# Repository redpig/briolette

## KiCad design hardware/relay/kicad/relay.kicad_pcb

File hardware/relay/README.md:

# Solar Relay — Disconnected Credstick-to-Credstick Payments

## The Problem

The credstick-to-credstick flow requires a phone as NFC relay. But:

- Phone batteries die
- Rural areas may have no electricity for charging
- Some users may not own a smartphone
- Cash works everywhere — Briolette should too

We need a cheap, rugged, batteryless relay device that can facilitate
credstick payments without a phone, without internet, and without
external power.

## The Device: Solar Relay

A small, dedicated NFC reader/writer powered by solar + shake energy.
No screen of its own (or minimal LED indicators). Its only job: shuttle
APDUs between two credsticks, just like the phone PoS relay app.

```
┌──────────────────────────────────────┐
│  ┌──────────────────────────────┐   │
│  │     Solar Panel (top face)   │   │
│  │     ~40x30mm mono-Si cell    │   │
│  └──────────────────────────────┘   │
│                                      │
│  [1] [2] [3] [4]  ← 4 buttons      │
│                                      │
│  ● ● ●  ← 3 LEDs (power/send/recv) │
│                                      │
│  ══════════  NFC reader antenna     │
│  ║  TAP  ║  (marked zone)           │
│  ══════════                          │
│                                      │
│  ┌────────┐                          │
│  │ USB-C  │  ← Charge + firmware    │
│  └────────┘                          │
└──────────────────────────────────────┘
       ~70mm x 45mm x 8mm
```

## Key Difference from Credstick

The credstick is an NFC **tag** (passive, powered by the reader's field).
The relay is an NFC **reader** (active, generates the RF field). This is
the critical distinction — the relay powers the credsticks, not the other
way around.

## Hardware Spec

### Core Components

| Component | Part | Notes |
|-----------|------|-------|
| MCU | nRF52840-QIAA | Same as credstick — shared firmware tooling |
| NFC frontend | PN7150 or PN532 | NFC reader/writer IC (not tag mode) |
| Solar cell | 40x30mm mono-Si | ~80-150mW in direct sun, ~5-15mW shade |
| Supercap | 2x 10F 3V (20F total) | Larger than credstick for reader power |
| Piezo harvester | Same as credstick | Supplemental, for pocket carry |
| Buttons | 4x 3mm tactile switches | PIN entry (see button spec) |
| LEDs | 3x 0402 (R/G/B) | Power status, send, receive |
| USB-C | GCT USB4135-GF-A | Charge + DFU |
| Charge controller | BQ25504 | Ultra-low-power solar MPPT harvester |

### Why PN7150/PN532 Instead of nRF52840's NFC?

The nRF52840's built-in NFC peripheral is **tag-only** (Type 2/4 Tag
emulation). It cannot generate an NFC field or act as a reader. To read
credsticks, we need a dedicated NFC reader IC:

- **PN7150**: NXP's NFC controller with reader/writer + P2P + card
  emulation. I2C interface. Low power (~20mA active). Best option.
- **PN532**: Older but widely available. SPI/I2C/UART. ~100mA active
  (higher power). Good for prototyping.

The nRF52840 drives the PN7150 over I2C and handles the Briolette
protocol logic. The PN7150 handles the RF layer.

### Power Budget

**NFC reader is the expensive part:**

| Operation | Current | Duration | Energy |
|-----------|---------|----------|--------|
| PN7150 field on (reader) | 20-50mA | 3-5s per tap | 60-250mAs |
| nRF52840 active | 5mA | 5s per tap | 25mAs |
| LED indicator | 5mA | 1s | 5mAs |
| Total per tap | | | ~90-280mAs |
| Total per transaction (4 taps) | | | ~360-1120mAs |

At 3V, a single 4-tap transaction costs **~1-3.4J**.

**Supercap budget (20F at 3V):**
- Usable energy: 0.5 x 20 x (9-4) = **50J**
- Transactions per charge: **~15-50**
- USB-C recharge: ~60 seconds

**Solar budget:**
- Direct sun: 80-150mW → 288-540J per hour → **80-160 transactions/hour**
- Overcast: 10-30mW → 36-108J per hour → **10-30 transactions/hour**
- Indoor light: 1-5mW → 3.6-18J per hour → **1-5 transactions/hour**
- Shade outdoors: 5-15mW → 18-54J per hour → **5-15 transactions/hour**

**In direct sun, the relay is effectively unlimited.**

### BQ25504 Solar MPPT

The BQ25504 is a nano-power boost charger with MPPT (Maximum Power Point
Tracking). It efficiently harvests from solar cells as low as 100mV
input and charges the supercap. Key specs:

- Input voltage: 100mV–5.5V (works with any small solar cell)
- Quiescent current: 330nA (virtually zero idle drain)
- MPPT efficiency: 80-90%
- Cold start: 330mV minimum (small light is enough to boot)

This means the relay can cold-start from a dead supercap just by
sitting in sunlight for a few minutes.

## Operating Modes

### 1. Solar Idle (Default)

Solar cell charges supercap via BQ25504. No NFC activity. LEDs off.
Power LED blinks once every 10s to show charge state:
- Green: >50% charge
- Yellow: 20-50%
- Red: <20%

### 2. Transaction Mode (Button Press)

User presses button 1 to start a relay session. The flow mirrors
`receiver.proto` (Initiate → Transact → Transfer):

```
Press [1] → Green LED on → "Ready"

Tap receiver → Blue LED blinks → READ_TICKET (0x11)
              → Blue LED solid → got ticket

Tap sender   → Relay sends INITIATE (0x10) + TRANSACT (0x20)
(tap 1)      → Credstick e-ink shows: "Pay 5 tokens?"
              → Returns unsigned tokens (proposal)
              → Blue LED solid → got proposal

              [User lifts credstick, reads display, enters PIN
               if required — all off the relay]

Tap sender   → Relay sends TRANSFER (0x30) with accept=true
(tap 2)      → Credstick checks PIN was entered (if needed)
              → BLS signs tokens, returns signatures
              → Blue LED solid → got signed tokens

Tap receiver → Relay sends RECEIVE (0x31) with signed tokens
              → Green LED flash 3x → done!
              → (or Red LED flash 3x → failed)
```

**Critical UX: the sender's credstick displays the proposed amount
on its e-ink screen during tap 1, and the user enters PIN between
taps.** The relay cannot forge the amount because the credstick
independently shows the actual APDU payload amount. The user
confirms by choosing to tap again — the physical tap IS consent.
No button press during NFC contact is ever required.

See `button-pin-auth.md` for the full PIN-between-taps flow.

### 3. Fixed-Amount Mode (Merchant Use)

For a merchant who always charges the same amount (e.g., a bus fare):

1. Press and hold [1] during power-on → enters config mode
2. Use buttons [1-4] to set amount (binary or digit-by-digit)
3. Amount is stored in flash
4. Every subsequent button press starts a transaction for that amount

This eliminates the need for a phone entirely for simple, fixed-price
transactions (transit, vending, market stalls).

### 4. Variable-Amount Mode

For variable amounts without a screen, the relay can accept amount
input via button presses:

- Buttons [1-4] map to digits or increments
- Quick-press sequences: [2][3] = 23 tokens
- Long-press [4] = confirm amount
- LED blinks N times to confirm the entered amount

This is clunky but functional. For better UX, pair with a phone running
the PoS app — but the relay works standalone for emergencies.

## PIN Authorization on the Relay

The 4 buttons also serve as PIN entry (see `button-pin-auth.md`).
Before the relay starts a transaction, the operator can optionally
require a PIN:

1. Power on → enter 4-digit PIN via buttons
2. Green LED = authorized, relay is active for N minutes or transactions
3. Wrong PIN → red LED, lockout after 3 failures

This prevents unauthorized use if the relay is stolen.

## BOM (Estimated)

| Component | Qty 10 | Qty 1000 |
|-----------|--------|----------|
| nRF52840 | $3.80 | $3.20 |
| PN7150 | $3.50 | $2.50 |
| Solar cell (40x30mm) | $2.00 | $0.80 |
| BQ25504 | $3.50 | $2.80 |
| Supercaps (2x 10F) | $6.00 | $4.00 |
| Piezo harvester | $5.00 | $2.00 |
| 4x tactile buttons | $0.60 | $0.32 |
| 3x LEDs | $0.30 | $0.15 |
| USB-C connector | $0.60 | $0.35 |
| PCB + passives | $6.00 | $2.00 |
| Enclosure | $3.00 | $0.50 |
| **Total** | **~$34** | **~$19** |

At scale, this is a **sub-$20 device** — comparable to a basic
calculator or kitchen timer. Cheap enough to distribute to rural
merchants or community centers.

## Use Cases

### Rural Market

A village market has no reliable electricity. Each vendor has a solar
relay clipped to their stall. Customers carry credsticks. Payments
happen all day powered by sunlight. At the end of the day, vendors
tap their credstick to a phone (when one is available) to sweep
accumulated tokens to a validated wallet.

### Transit / Bus

A bus driver has a relay mounted on the dashboard. Fixed fare mode.
Passenger taps credstick → fare deducted → rider boards. Solar charges
the relay during the day. USB-C from the bus's 12V system as backup.

### Emergency / Disaster

Grid is down, cell towers are down. People still need to transact.
Solar relays + credsticks provide a fully disconnected, self-powered
payment system. No internet, no electricity, no phone required.

### Peer-to-Peer in the Field

Two hikers want to split a cost. One pulls out a solar relay from their
pack, both tap credsticks. Works on a mountaintop with zero infrastructure.

## Credstick Storage Considerations

For long periods of disconnected operation, credsticks accumulate
unvalidated tokens. The credstick flash should accommodate:

| Scenario | Tokens | Storage (~200 bytes/token) |
|----------|--------|---------------------------|
| Light daily use (5 txns/day, 7 days) | 35 | ~7 KB |
| Heavy daily use (20 txns/day, 7 days) | 140 | ~28 KB |
| Extended disconnected (30 days) | 600 | ~120 KB |
| Extreme (3 months disconnected) | 1800 | ~360 KB |

The nRF52840 has 1 MB flash. After firmware (~256 KB) and bloom
filter (~64 KB), there's **~680 KB** available for token storage —
enough for ~3400 tokens, covering months of disconnected operation.

For extra safety, an external QSPI flash (e.g., 4 MB MX25R4035F, $0.50)
could extend storage to tens of thousands of tokens.

## Relationship to Phone PoS App

The solar relay and the phone PoS app are functionally identical — both
are dumb NFC relays that shuttle APDUs. The difference:

| | Phone PoS App | Solar Relay |
|---|---------------|-------------|
| Screen | Full touchscreen | 3 LEDs |
| Input | Touch keyboard | 4 buttons |
| Power | Phone battery | Solar + supercap |
| Cost | $0 (app on existing phone) | ~$19 at scale |
| Internet | Optional (for logging) | Never needed |
| UX | Rich, guided | Minimal, LED-guided |

They're complementary. The phone app is better UX. The solar relay is
the fallback when phones aren't available.

## Future: Deposit Box Mode (v2)

Beyond real-time relay, the solar relay can evolve into a **deposit box**
("cryptographic village bank") for deferred payments. See
`../stick/docs/deferred-payment.md` for the full design.

In this mode, senders prepare and sign payments on their credstick alone
(using a saved recipient code), then drop off pre-signed tokens at the
relay later. Recipients collect deposits by tapping the relay and proving
ticket ownership.

### Relay Storage for Deposits

The v1 relay hardware should account for this by including external flash:

| Storage | Capacity | Deposits (~300 bytes each) | Cost |
|---------|----------|---------------------------|------|
| nRF52840 internal (spare) | ~200 KB | ~600 | $0 |
| External QSPI (MX25R4035F) | 4 MB | ~13,000 | ~$0.50 |

For a village relay serving a few dozen daily transactions, internal flash
suffices. The QSPI footprint should be on the v1 PCB even if not populated
initially — allows the upgrade path without a board respin.

### Merchant Registry

The relay can store a local registry mapping short codes (e.g., "001") to
merchant `SignedTicket` data. This enables the "type in merchant code on
credstick, resolve at relay" flow. Storage: ~300 bytes per merchant ×
100 merchants = ~30 KB. Trivially fits in flash.

### APDU Reservations

The v1 relay firmware should reserve INS bytes 0x40-0x4F for deposit box
commands (DROP_OFF, CHECK_DEPOSITS, COLLECT). No implementation needed
for v1 — just don't assign those bytes to other functions.

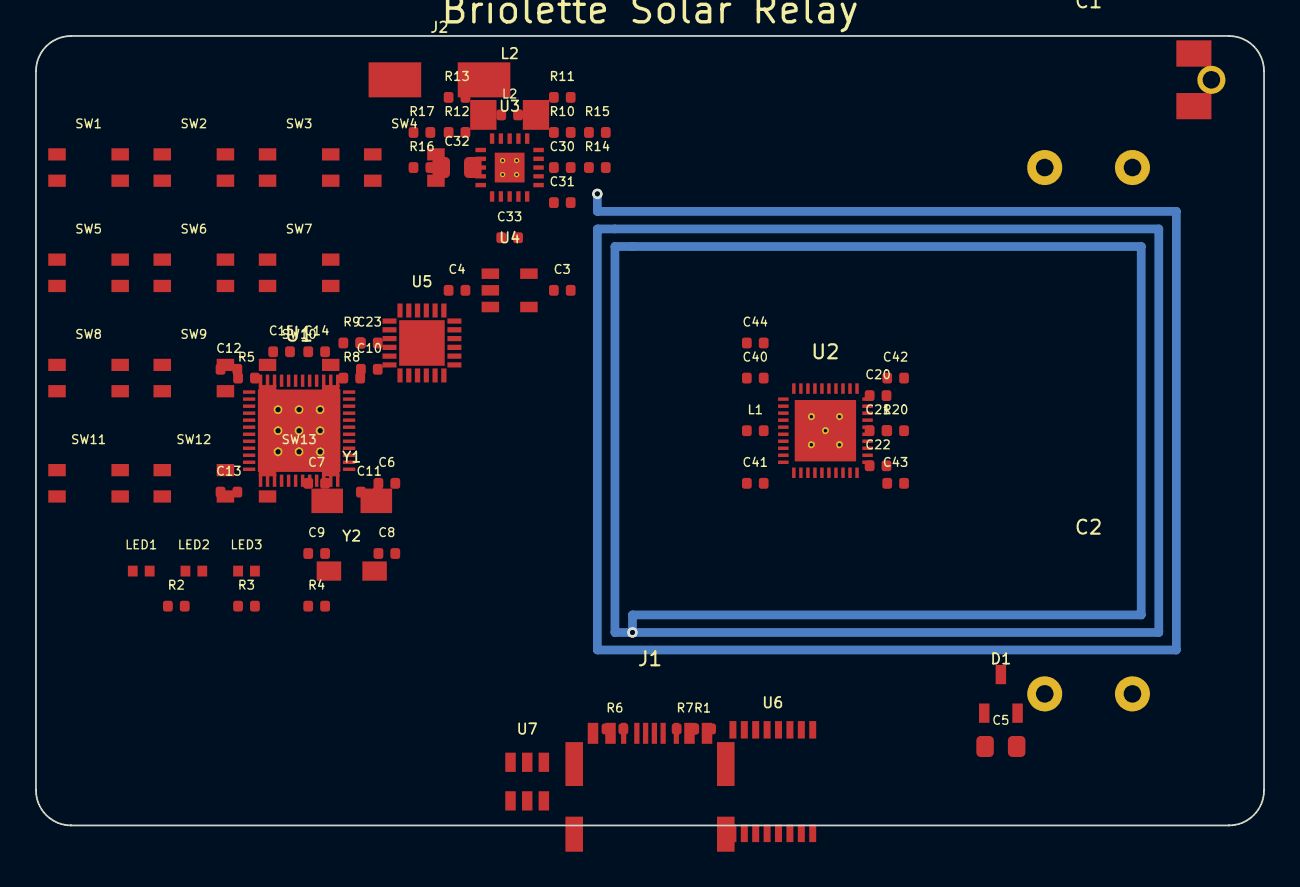
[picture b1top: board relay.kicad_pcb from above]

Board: 4 copper layers, 70.0 x 45.0 mm, 78 parts (0 on the bottom side), 33 nets.

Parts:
C1, C2: 10F 3V; Supercap_Cylindrical_14mm
C3, C4, C33: 10uF; C_0402_1005Metric
C5: 100uF; C_0805_2012Metric
C6, C7: 12pF; C_0402_1005Metric
C8, C9: 6.8pF; C_0402_1005Metric
C10, C11, C12, C13, C14, C15, C20, C21, C22, C23, C30, C43, C44: 100nF; C_0402_1005Metric
C31: 4.7uF; C_0402_1005Metric
C32: 22uF; C_0805_2012Metric
C40, C41: 150pF; C_0402_1005Metric
C42: 27pF; C_0402_1005Metric
D1: BAT54S; SOT-23
J1: USB4135-GF-A; USB_C_GCT_USB4135
J2: Solar_Cell; SolderWirePad_1x02_P5.08mm_D1.5mm
J3: PPA-1014; Piezo_Cantilever_25x5mm
L1: 390nH; L_0402_1005Metric
L2: 2.2uH; L_0402_1005Metric
L2#2: 2.2uH; L_Coilcraft_LPS4018
LED1: RED; LED_0402_1005Metric
LED2: GREEN; LED_0402_1005Metric
LED3: BLUE; LED_0402_1005Metric
R1, R5: 10k; R_0402_1005Metric
R2, R3, R4: 1k; R_0402_1005Metric
R6, R7: 5.1k; R_0402_1005Metric
R8, R9: 4.7k; R_0402_1005Metric
R10, R12, R14, R16: 5.76M; R_0402_1005Metric
R11: 8.06M; R_0402_1005Metric
R13, R17: 8.87M; R_0402_1005Metric
R15: 13.3M; R_0402_1005Metric
R20: 10R; R_0402_1005Metric
SW1: KEY_1; SW_SPST_3x3mm
SW2: KEY_2; SW_SPST_3x3mm
SW3: KEY_3; SW_SPST_3x3mm
SW4: KEY_CLR; SW_SPST_3x3mm
SW5: KEY_4; SW_SPST_3x3mm
SW6: KEY_5; SW_SPST_3x3mm
SW7: KEY_6; SW_SPST_3x3mm
SW8: KEY_7; SW_SPST_3x3mm
SW9: KEY_8; SW_SPST_3x3mm
SW10: KEY_9; SW_SPST_3x3mm
SW11: KEY_DOT; SW_SPST_3x3mm
SW12: KEY_0; SW_SPST_3x3mm
SW13: KEY_OK; SW_SPST_3x3mm
U1: nRF52840; QFN-48-6x6mm
U2: PN7150; HVQFN-40-5x5mm
U3: BQ25504; QFN-20-3.5x3.5mm
U4: AP2112K-3.3; SOT-23-5
U5: TCA8418; WQFN-24-4x4mm
U6: IP4292CZ12; TSSOP-16_4.4x5mm_P0.65mm
U7: TPS2553; SOT-23-6
Y1: 32MHz; Crystal_SMD_3225-2Pin_3.2x2.5mm
Y2: 32.768kHz; Crystal_SMD_3215-2Pin_3.2x1.5mm

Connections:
GND: C1.2, C2.2, C3.2, C4.2, C5.2, C6.2, C7.2, C8.2, C9.2, C10.2, C11.2, C12.2, C13.2, C14.2, C15.2, C20.2, C21.2, C22.2, C23.2, C30.2, C31.2, C32.2, C33.2, C40.2, C41.2, C42.2, C43.2, C44.2, J1.A1, J1.B1, J1.S1, J2.2, J3.2, J3.MP, LED1.2, LED2.2, LED3.2, R1.2, R6.2, R7.2, R11.2, R13.2, R15.2, R17.2, U1.33, U1.39, U1.49, U2.1, U2.2, U2.8, U2.11, U2.24, U2.25, U2.30, U2.37, U2.41, U3.2, U3.14, U3.17, U3.21, U4.2, U5.24, U5.25, U6.8, U6.9, U7.2
I2C_SCL: R9.2, U1.31, U2.10, U5.15
I2C_SDA: R8.2, U1.30, U2.9, U5.14
KEY_COL0: SW1.1, SW1.3, SW5.1, SW5.3, SW8.1, SW8.3, SW11.1, SW11.3, U5.7
KEY_COL1: SW2.1, SW2.3, SW6.1, SW6.3, SW9.1, SW9.3, SW12.1, SW12.3, U5.8
KEY_COL2: SW3.1, SW3.3, SW7.1, SW7.3, SW10.1, SW10.3, SW13.1, SW13.3, U5.9
KEY_COL3: SW4.1, SW4.3, U5.10
KEY_INT: U1.15, U5.16
KEY_ROW0: SW1.2, SW1.4, SW2.2, SW2.4, SW3.2, SW3.4, SW4.2, SW4.4, U5.1
KEY_ROW1: SW5.2, SW5.4, SW6.2, SW6.4, SW7.2, SW7.4, U5.2
KEY_ROW2: SW8.2, SW8.4, SW9.2, SW9.4, SW10.2, SW10.4, U5.3
KEY_ROW3: SW11.2, SW11.4, SW12.2, SW12.4, SW13.2, SW13.4, U5.4
KEY_RST: U1.16, U5.19
LBST: L2.1, L2#2.1, U3.18, U3.19
LED_B: LED3.1, R4.2, U1.14
LED_G: LED2.1, R3.2, U1.12
LED_R: LED1.1, R2.2, U1.11
NFC_IRQ: U1.25, U2.7
NFC_RX: C42.1, R20.1, R20.2, U2.23
NFC_TX1: C40.1, L1.1, L1.2, U2.28
NFC_TX2: C41.1, U2.29
NFC_VEN: U1.26, U2.35
USB_DM: J1.A7, J1.B7, U6.1, U6.16
USB_DP: J1.A6, J1.B6, U6.2, U6.15
VBAT_OK: U1.9, U3.9
VBUS: C5.1, D1.3, J1.A4, J1.B4, U6.5, U6.12, U7.1, U7.3
VCC: C3.1, C10.1, C11.1, C12.1, C13.1, C14.1, C15.1, C20.1, C21.1, C22.1, C23.1, C43.1, C44.1, R2.1, R3.1, R4.1, R5.1, R8.1, R9.1, U1.3, U1.13, U1.42, U1.43, U2.3, U2.4, U2.5, U2.26, U2.27, U2.38, U4.5, U5.13
VSCAP: C1.1, C2.1, C4.1, C31.1, C32.1, C33.1, D1.1, D1.2, R10.1, R12.1, R14.1, U3.7, U3.8, U3.15, U3.16, U4.1, U4.3, U7.6
VSOLAR: C30.1, J2.1, J3.1, L2.2, L2#2.2, R16.1, U3.1, U3.20
XC1: C6.1, Y1.1
XC2: C7.1, Y1.2
XL1: C8.1, U1.5, Y2.1
XL2: C9.1, U1.6, Y2.2

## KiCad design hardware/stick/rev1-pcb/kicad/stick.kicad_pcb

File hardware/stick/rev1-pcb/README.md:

# Rev 1 — Custom PCB

First integrated board. All components on a single PCB targeting a
keychain or USB-stick form factor.

## Target Form Factor

**Keychain fob / thick USB stick:**
- ~60mm x 30mm x 6mm (roughly the size of a car key fob)
- USB-C connector on one end
- E-ink display window on one face
- NFC antenna as PCB trace coil (no external antenna)
- Keyring hole on opposite end from USB-C

```
  ┌─────────────────────────────────────────┐
  │  ○  ┌─────────────────────┐             │
  │ key │                     │  ┌────────┐ │
  │ring │    E-Ink Display    │  │ USB-C  │ │
  │     │     1.02" / 1.54"   │  └────────┘ │
  │     └─────────────────────┘             │
  │     [◄]                 [►]             │
  │    ╔══════════════════════════╗          │
  │    ║   NFC Trace Antenna     ║          │
  │    ╚══════════════════════════╝          │
  └─────────────────────────────────────────┘
         ~60mm x 30mm (top view)
```

The two buttons [◄] [►] sit below the display, aligned with the
"No" and "Yes" labels shown during transaction confirmation. They
also serve as PIN entry (left/right + timing), balance navigation,
and general UI control. See `docs/button-pin-auth.md` for details.

## Layer Stack (4-layer PCB)

| Layer | Purpose |
|-------|---------|
| Top | Components, USB-C, display connector, buttons |
| Inner 1 | Ground plane |
| Inner 2 | Power plane + I2C/SPI routing |
| Bottom | NFC antenna trace coil |

## Block Diagram

```
                    USB-C
                      │
              ┌───────┴───────┐
              │  ESD Protect   │
              │  (IP4292CZ12)  │
              └───────┬───────┘
                      │ VBUS
              ┌───────┴───────┐     ┌──────────────────┐
              │  Charge path   │     │ Supercaps        │
              │  (current-     │─────│ 2× 5F 3V (par.) │
              │  limited)      │     │ = 10F total      │
              └───────────────┘     └────────┬─────────┘
                                             │ VSCAP (2.0-3.0V)
              ┌──────────────────────────────┴─┐
              │  LDO or buck-boost               │
              │  (3.0V → stable 3.3V or direct)  │
              └───────────┬─────────────────────┘
                          │ VCC
              ┌───────────┴───────────┐
              │       nRF52840        │     ┌──────────────┐
              │       (QFN-48)        │─7816│  SIM Card    │
              │                       │     │  (nano-SIM)  │
              │  CryptoCell 310       │     │  push-push   │
              │                       │     └──────────────┘
              │  NFC1/NFC2 ───────────┼──── PCB Trace Antenna
              │                       │
              │  SPI ─────────────────┼──── E-Ink Display (FPC)
              │                       │
              │  GPIO ────────────────┼──── Button(s) + Piezo
              └───────────────────────┘

              ┌───────────────────────┐
              │  Piezo Harvester      │
              │  (cantilever + rect.) │──── VSCAP (trickle)
              └───────────────────────┘
```

## Design Files

KiCad project files will be added here as the design progresses.

```
rev1-pcb/
├── README.md          # This file
├── BOM.md             # Production bill of materials
├── kicad/             # KiCad project (future)
│   ├── stick.kicad_pro
│   ├── stick.kicad_sch
│   └── stick.kicad_pcb
├── gerbers/           # Manufacturing files (future)
└── 3d/                # Enclosure models (future)
```

## Design Decisions

- **nRF52840 QFN-48** (not WLCSP): QFN is hand-solderable with hot air
  for prototyping. WLCSP requires reflow and X-ray inspection.
- **Nano-SIM push-push connector** (Molex 78800-0001): Low-profile
  (1.25mm height), flush-insert push-push mechanism. ISO 7816 interface
  (SIM_IO, SIM_CLK, SIM_RST). User-replaceable SIM card provides the
  same tamper-resistant SE functions as the old ATECC608B (P-256 ECDSA,
  key storage, monotonic counters) but is swappable and field-upgradeable.
  Production-robust: standard connector used in billions of phones.
- **NFC as PCB trace**: Eliminates a discrete antenna component. The
  bottom copper layer has a rectangular spiral trace tuned to 13.56 MHz
  with a matching network (two capacitors).
- **Supercapacitors (2× 5F 3V in parallel = 10F)**: Primary energy
  storage. Infinite cycle life (>1M cycles), no degradation, no fire
  risk, wide temperature range. 25J stored, ~96 transactions per full
  charge. Self-discharge (~5-10%/day) offset by piezo harvesting.
  USB-C recharge takes seconds, not hours.
- **Piezo energy harvester**: Cantilever-mounted piezoelectric element
  converts keychain motion into electrical energy. Passive carry offsets
  supercap self-discharge; deliberate shaking adds ~10-50mJ in 10s.
  Rectified via a Schottky bridge + small buffer cap into VSCAP rail.
- **No battery**: Deliberate choice for infinite device lifetime. No
  capacity fade, no swelling, no replacement needed. The supercap +
  piezo + USB-C combination covers all use cases.
- **1.02" e-ink preferred**: Smaller display fits the keychain target.
  128x80 pixels is enough for balance + 2-line status. The 1.54" is an
  option if we relax to credit-card size.

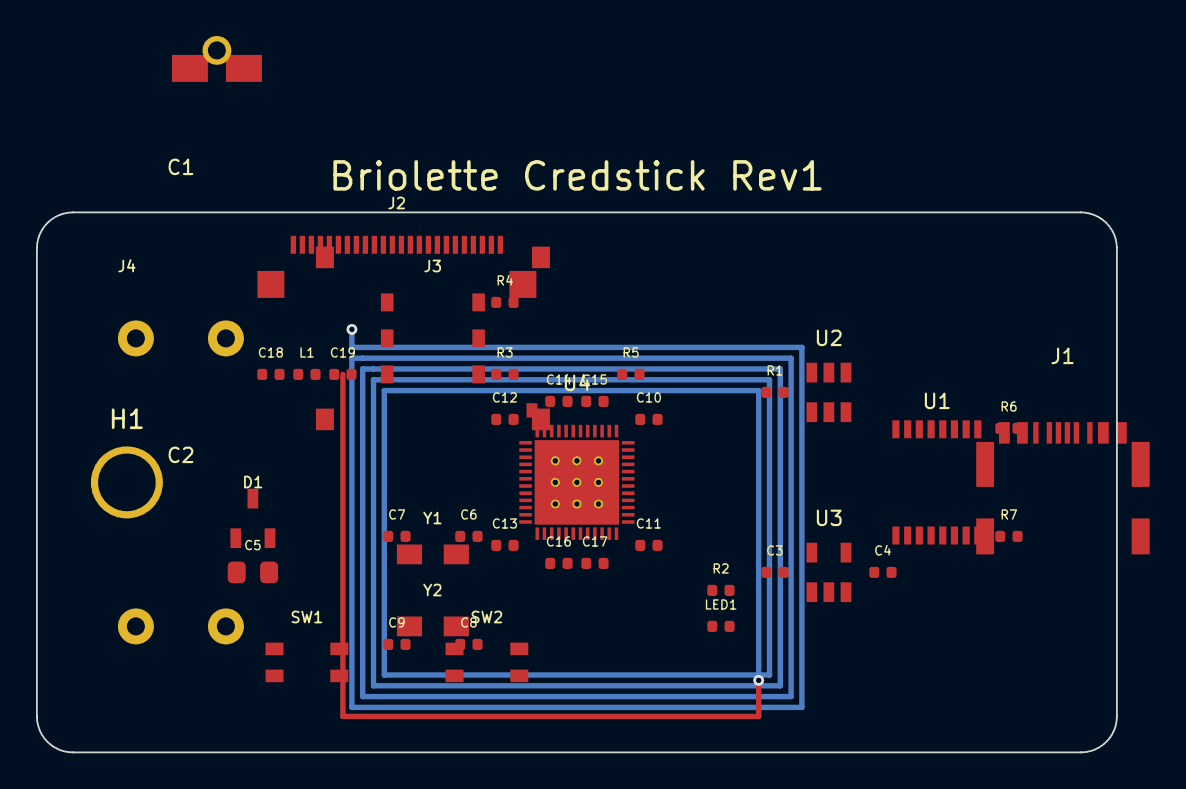
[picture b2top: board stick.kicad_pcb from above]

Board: 4 copper layers, 60.0 x 30.0 mm, 42 parts (0 on the bottom side), 32 nets.

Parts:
C1, C2: 5F 3V; Supercap_Cylindrical_14mm
C3, C4: 10uF; C_0402_1005Metric
C5: 100uF; C_0805_2012Metric
C6, C7: 12pF; C_0402_1005Metric
C8, C9: 6.8pF; C_0402_1005Metric
C10, C11, C12, C13, C14, C15, C16, C17: 100nF; C_0402_1005Metric
C18, C19: 180pF; C_0402_1005Metric
D1: BAT54S; SOT-23
H1: Keyring; MountingHole_3.2mm_M3
J1: USB4135-GF-A; USB_C_GCT_USB4135
J2: GDEY0154D67; FPC_24pin_0.5mm
J3: Nano-SIM Push-Push; NanoSIM_Molex_78800
J4: PPA-1014; Piezo_Cantilever_25x5mm
L1: 390nH; L_0402_1005Metric
LED1: Green; LED_0402_1005Metric
R1, R3, R4, R5: 10k; R_0402_1005Metric
R2: 1k; R_0402_1005Metric
R6, R7: 5.1k; R_0402_1005Metric
SW1: BTN_L; SW_SPST_3x3mm
SW2: BTN_R; SW_SPST_3x3mm
U1: IP4292CZ12; TSSOP-16_4.4x5mm_P0.65mm
U2: TPS2553; SOT-23-6
U3: AP2112K-3.3; SOT-23-5
U4: nRF52840; QFN-48-6x6mm
Y1: 32MHz; Crystal_SMD_3225-2Pin_3.2x2.5mm
Y2: 32.768kHz; Crystal_SMD_3215-2Pin_3.2x1.5mm

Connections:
BTN_L: SW1.1, SW1.3, U4.34
BTN_R: SW2.1, SW2.3, U4.35
CC1: J1.A5, R6.1
CC2: J1.B5, R7.1
DEC1: C14.1, U4.27
DEC4: C15.1, U4.10
EPD_BUSY: J2.18, U4.43
EPD_DC: J2.16, U4.41
EPD_RST: J2.17, U4.42
GND: C1.2, C2.2, C3.2, C4.2, C5.2, C6.2, C7.2, C8.2, C9.2, C10.2, C11.2, C12.2, C13.2, C14.2, C15.2, C16.2, C17.2, C18.2, C19.2, D1.3, J1.A1, J1.B1, J1.S1, J2.1, J2.2, J2.12, J2.MP, J3.C5, J3.SH, LED1.2, R1.2, R2.2, R6.2, R7.2, SW1.2, SW1.4, SW2.2, SW2.4, U1.8, U1.9, U2.2, U3.2, U4.49
ILIM: R1.1, U2.4
LED: LED1.1, R2.1, U2.5, U4.46
NFC1: C18.1, L1.1, U4.32
NFC_ANT1: C19.1, L1.2
PIEZO_P: D1.1, J4.1
SIM_CLK: J3.C3, U4.15
SIM_DET: J3.CD, R4.2, U4.48
SIM_IO: J3.C7, R3.2, U4.14
SIM_RST: J3.C2, U4.47
SPI_CS: J2.15, U4.40
SPI_MOSI: J2.14, U4.39
SPI_SCK: J2.13, U4.38
USB_DM: J1.A7, J1.B7, U1.1, U1.16, U4.6
USB_DP: J1.A6, J1.B6, U1.2, U1.15, U4.7
VBUS: J1.A4, J1.B4, U1.5, U1.12, U2.1, U4.8
VCC: C4.1, C10.1, C11.1, C12.1, C13.1, C16.1, C17.1, J2.11, J3.C1, J3.C6, R3.1, R4.1, R5.1, U3.5, U4.5, U4.12, U4.20, U4.28, U4.37
VSCAP: C1.1, C2.1, C3.1, C5.1, D1.2, U2.6, U3.1, U3.3, U4.16
XC1: C6.1, U4.3, Y1.1
XC2: C7.1, U4.2, Y1.2
XL1: C8.1, U4.25, Y2.1
XL2: C9.1, U4.26, Y2.2
~RESET: R5.2, U4.36

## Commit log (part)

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2026-03-09 fix: correct truncated crate imports in wallet tests
    The wallet test module had truncated import names (ette_clerk, ette_registrar)
    instead of the full crate names (briolette_clerk, briolette_registrar),
    preventing test compilation.
    https://claude.ai/code/session_01DAqwMnBQGaP2NES63jLv2t
2026-03-09 Replace xaptum ECDAA C library with pure Rust implementation
    Replace the C FFI wrapper around libecdaa with a native Rust ECDAA
    implementation using substrate-bn (BN254 pairing-friendly curve).
    The public API in v0.rs is preserved: generate_wallet_keypair,
    generate_issuer_keypair, issue_credential, sign, verify,
    randomize_credential, credential_from_signature, deflate/inflate
    signature, and credential_in_group all maintain the same signatures
2026-03-10 Add split-key signing protocol (Brickell & Li style)
    Implements additive key splitting for ECDAA signatures where
    sk = card_sk + host_sk. The smart card only performs G1 scalar
    multiplications and Fr arithmetic — no pairings needed on-card.
    This enables Javacard/SIM-based wallets following the PAYGO model.
    Includes SmartCard trait, MockCard implementation, split key
    generation, split signing protocol, and 19 tests covering
2026-03-10 Validate split amounts in token_is_extension to prevent value inflation
    token_is_extension() previously accepted extensions containing split tags
    without checking whether the split amount exceeded the token's original
    descriptor value. A malicious wallet could extend a token history with
    an inflated split amount (e.g., claiming 15 on a token worth 10) and
    have it accepted as a legitimate extension.
    Now checks all new history entries for SplitValue tags and rejects the
2026-03-10 Add analysis of spending off expired tickets during partitions
    During a network partition, a wallet's short-lived tickets expire while
    tokens remain bound to them. The design already allows transfers to
    expired tickets (clerk.proto:32), and Token::transfer() doesn't check
    expiration. But SignedTicket::verify() rejects expired tickets in
    historical entries, freezing the tokens.
    Proposes relaxing verification: only enforce ticket expiration on the
2026-03-11 Add Bitcoin L2 bridge implementation alongside Ethereum
    Adds a parallel Bitcoin L1 integration for Briolette, enabling it to
    operate as either an Ethereum or Bitcoin L2. Both implementations coexist
    in the same codebase for reference comparison.
    New files:
    - l1.rs: Chain-agnostic L1Client trait extracted from ethereum.rs
    - bitcoin.rs: Bitcoin L1 client using Taproot deposits, OP_RETURN epoch
2026-03-11 Add Terminated stutter step to GossipConvergence
    Prevents deadlock when all honest wallets converge at MaxEpoch
    and no further actions are enabled. Same pattern as the other specs.
    Verified: 81 distinct states, all safety invariants + EventualConvergence
    liveness hold.
    https://claude.ai/code/session_01GwHJwU12qdRAMvY17Pi1iQ
2026-03-11 Add A2A and x402 protocol support for agent commerce
    Implements two complementary HTTP protocols on top of briolette's
    existing gRPC infrastructure:
    - A2A (Agent-to-Agent): Agent Card discovery at /.well-known/agent.json
    and JSON-RPC 2.0 task lifecycle mapping Receiver's initiate/transact/
    transfer flow to A2A task states.
    - x402 (HTTP 402 Payment Required): axum middleware that paywalls HTTP
2026-03-11 Add QR scanner, transfer display, history, and iOS Compose integration
    Completes the core mobile wallet UX with all QR-based payment flows:
    CameraX + ML Kit QR scanner (Android):
    - Full-screen camera preview with barcode analysis
    - Runtime camera permission request
    - Viewfinder overlay and scan-once guard
    - Automatic QR format detection (raw base64 or JSON envelope)
2026-03-11 Add hardware attestation verification for Android and iOS registrar
    Implement Android Key Attestation (X.509 cert chain with ASN.1
    KeyDescription) and iOS App Attest (CBOR attestation object with x5c)
    verification in the registrar. The registrar now verifies real hardware
    attestation before issuing ECDAA credentials, binding TTC nonces to
    hardware-derived identifiers instead of self-reported hw_id.
    - Add attestation.rs with verify_android_attestation() and
2026-03-11 Add proto definitions for security-level-tiered policy
    Add SecurityLevelPolicy and SecurityLevelGroupKeys messages to
    ExtendedEpochData, and granted_security_level field to RegisterReply.
    This is the proto groundwork for differentiating ticket lifetime and
    other policies based on hardware attestation security level (LOW for
    software-only wallets, HIGH for smartcard-backed wallets).
    https://claude.ai/code/session_01TM1rFxbipYtvAkh4Vt7My7
2026-03-11 Allow user to freely choose MEDIUM or HIGH security mode
    Remove the NFC hardware gate on the High chip so users can always
    select either mode. When HIGH is chosen without NFC available, a
    warning is shown instead of disabling the option.
    https://claude.ai/code/session_01TM1rFxbipYtvAkh4Vt7My7
2026-03-12 Add compile-time conditional for EC math backend
    Split ECMath into two implementations selected at build time:
    - applet-sim/ECMath.java: BigInteger (jCardSim simulator, default)
    - applet-hw/ECMath.java: JCMathLib (production JavaCard hardware)
    The build system automatically selects the backend based on whether
    JCMATHLIB_HOME is set or libs/JCMathLib.jar exists. Can also be
    forced with -PUSE_JCMATHLIB=true.
2026-03-12 Correct H-2 finding: JavaCard EC math stubs replaced with real implementations
    The applet now has two ECMath backends:
    - applet-sim/ECMath.java: BigInteger-based for jCardSim testing
    - applet-hw/ECMath.java: JCMathLib-based for real JavaCard hardware
    BrioletteApplet delegates to ECMath.* static methods; build flag selects
    backend. Downgrade from High to Medium — remaining work is hardware testing.
    https://claude.ai/code/session_01TM1rFxbipYtvAkh4Vt7My7
2026-03-12 Switch v1 (BLS12-381) to compressed point serialization
    Use Zcash/IETF compressed encoding for G1 (48 bytes) and G2 (96 bytes)
    instead of uncompressed (97/193 bytes). This makes v1 ECDAA signatures
    288 bytes — 19% smaller than v0's 356 bytes — while providing 128-bit
    security vs v0's ~100-bit.
    Key size changes:
    - G1: 97 → 48 bytes, G2: 193 → 96 bytes
2026-03-12 Add wallet recovery system: design doc, proto, TLA+ spec, and implementation
    Implements the recovery server and proof-of-binding protocol for recovering
    tokens from lost wallets. Wallets pre-register a recovery binding (ECDSA P-256
    backup key or peer wallet TTC credential) with the recovery server. After loss,
    the delegate proves authorization and receives replacement tokens from the mint.
    The old wallet's credential group is revoked to prevent double-spending.
    New files:
2026-03-13 Document NAC attestation architecture and manufacturer DAA vision
    Add docs/design/nac_attestation.md covering:
    - Why BLS12-381 keys can't live in platform keystores (P-256/RSA only)
    - How P-256 attestation gates NAC credential issuance (current model)
    - Target: manufacturer DAA credentials for smartcard attestation
    - Alternative: platform keystore pairing-friendly curve support
    - Security tier progression: LOW → MEDIUM → HIGH → HIGH+ → Ideal
2026-03-13 Supercap-primary power design, piezo harvesting, credstick-to-credstick protocol
    Power architecture reworked:
    - Supercaps (2x5F 3V) as sole energy storage — infinite cycle life
    - Piezo energy harvester offsets self-discharge from keychain motion
    - No battery: device lifetime limited only by component failure
    - 10F supercap supports 100+ transactions per USB-C charge (~30s)
    New doc: credstick-to-credstick payments via phone relay
2026-03-13 Add KiCad project for credstick Rev1 PCB (60x30mm, 4-layer)
    Hierarchical schematic with three sheets:
    - Power: USB-C → ESD (IP4292CZ12) → charge limiter (TPS2553) →
    supercaps (2×5F 3V) → LDO (AP2112K-3.3), plus piezo harvester
    rectifier (BAT54S) and CC pull-downs for USB UFP identification
    - MCU: nRF52840 QFN-48 with 32MHz/32.768kHz crystals, decoupling
    caps, and all GPIO assignments (I2C, SPI, NFC, USB, buttons, LED)
2026-03-14 Add missing gradle-wrapper.jar for mobile build
    https://claude.ai/code/session_01TM1rFxbipYtvAkh4Vt7My7
2026-03-14 Add OpenTitan migration plan for hardware-accelerated BLS12-381
    Documents the path from current ATECC608B + software BLS12-381 (2-3s)
    to OpenTitan OTBN-accelerated signing (target <400ms) to reach Visa
    tap-and-pay speed. Covers OTBN firmware requirements, SPI protocol
    design, power budget analysis, and phased migration steps.
    Key insight: OTBN's 256-bit wide registers should give 10-20x speedup
    on Fp381 modular arithmetic. Development can start today using the
2026-03-14 Add v2 destination binding analysis and credstick amount entry UX
    Two major design explorations:
    1. Ticket vs claim-code destination binding: Since double-spend detection
    uses previous_signature as the ECDAA basename (independent of the
    recipient), we can replace the ticket destination with a claim-hash
    commitment for stranger payments. Proposes both models coexisting
    via a Transfer oneof: ticket-bound for saved contacts, claim-code
2026-03-14 Add fuse module design doc: consumable secure hardware for double-spend prevention
    Explores shifting the secure hardware requirement from the wallet to a cheap,
    disposable fuse module where reading a fuse value physically destroys it.
    Wallets become commodity electronics, and double-spend prevention becomes a
    physical property rather than a computational one. Covers integration with
    NAC/TTC credential model, visual attestation, fuse economics, and the key
    property that fuse compromise enables double-spend but not token minting.
2026-03-14 Add recovery server unit tests and re-render OpenSCAD enclosure GIFs
    Add 11 unit tests for recovery server covering DB schema, hash functions,
    binding state management, and recovery log. Re-render credstick and relay
    case animated GIFs to reflect current SCAD models (credstick now includes
    SIM card slot).
    https://claude.ai/code/session_01TM1rFxbipYtvAkh4Vt7My7
2026-03-19 Fix use-after-free segfault: get plot filename before ClosePlot
    The primary segfault was in export_gerbers() where GetPlotFileName()
    was called after ClosePlot(). ClosePlot() frees the C++ plot
    controller's internal state, so the subsequent GetPlotFileName()
    accesses freed memory through the SWIG bindings, causing a segfault.
    Move GetPlotFileName() before ClosePlot() to read the filename while
    the plot state is still valid. Also add a null check on LoadBoard()
2026-03-19 Add missing UUIDs to all PCB elements for KiCad 8.0 compatibility
    KiCad 8.0 requires uuid on footprints, graphical items (gr_line,
    gr_arc, gr_rect, gr_text), dimensions, segments, vias, and zones.
    Missing UUIDs cause "Failed to load board" (exit 3).
    https://claude.ai/code/session_019dReYSafgEC1b8rTuLhQSc
2026-03-19 Add bisection test: relay headers/layers/setup only
    Relay's exact header structure with layers, stackup, setup, and
    board outline but no footprints/traces/zones. For isolating the
    parse failure.
    https://claude.ai/code/session_019dReYSafgEC1b8rTuLhQSc
